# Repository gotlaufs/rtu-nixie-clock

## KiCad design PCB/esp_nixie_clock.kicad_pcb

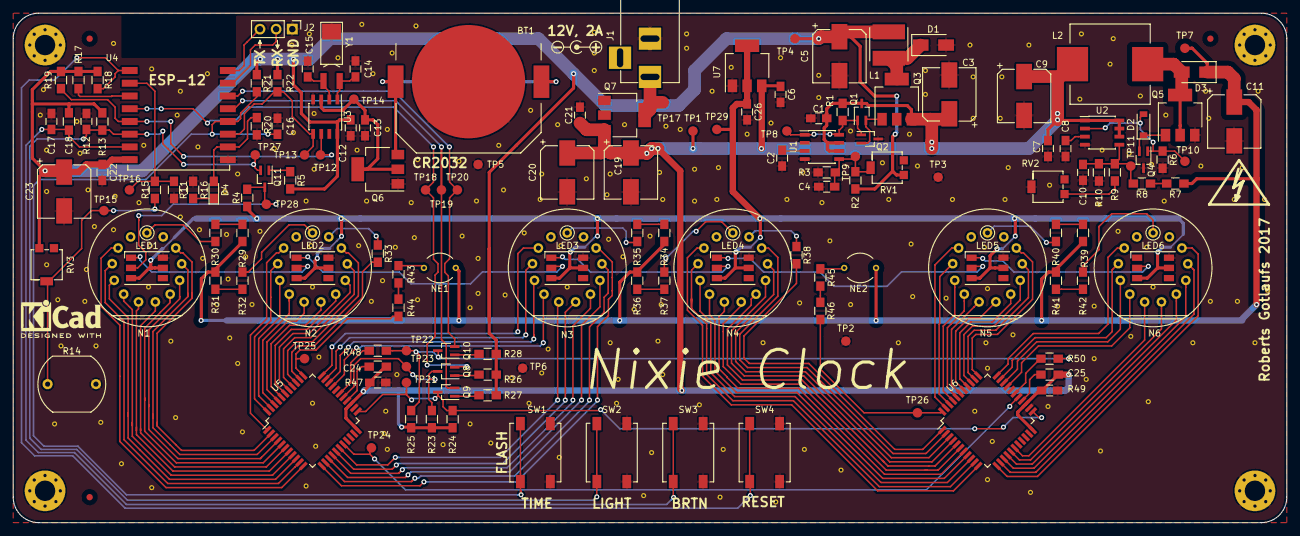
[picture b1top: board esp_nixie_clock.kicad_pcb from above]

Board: 2 copper layers, 200.0 x 80.0 mm, 161 parts (0 on the bottom side), 138 nets.

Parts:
BT1: CR2032; BATT_HOLDER
C1, C6, C7, C12, C13, C16, C17, C18, C21, C22, C24, C25, C26: 100n; C_0805_HandSoldering
C2: 270p; C_0805_HandSoldering
C3, C5, C9, C19: 220u; CP_Elec_8x10
C4, C10: 10n; C_0805_HandSoldering
C8: 680p; C_0805_HandSoldering
C11: 2.2u; CP_Elec_8x10
C14, C15: 6p; C_0805_HandSoldering
C20: 1u; CP_Elec_8x10
C23: 10u; CP_Elec_8x10
D1: SS13 R3G; D_SMA
D2: 1n4148; D_SOD-123
D3: RS1GTR; D_SMA
D4: LED; LED_0805_HandSoldering
F1, F2, F3: Fiducial; Fiducial_1mm_Dia_2.54mm_Outer_CopperTop
J1: Power Jack; BARREL_JACK
J2: Conn_01x03_Male; Pin_Header_Straight_1x03_Pitch2.54mm
L1: 100u; L_100u
L2: 150u; L_Wuerth_WE-PD-Typ-LS_Handsoldering
LED1, LED2, LED3, LED4, LED5, LED6: WS2812; LED_WS2812-PLCC6
MK1, MK2, MK3, MK4: Mounting_Hole_PAD; MountingHole_3.2mm_M3_Pad_Via
N1, N2, N3, N4, N5, N6: IN-14
NE1, NE2: Lamp_Neon; NE-2
Q1, Q8, Q9, Q10, Q11: BC847BW; SOT-323_SC-70_Handsoldering
Q2, Q4: BC857W; SOT-323_SC-70_Handsoldering
Q3, Q6, Q7: NTF5P03T3G; SOT-223-3_TabPin2
Q5: IPN70R900P7SATMA1; SOT-223-3_TabPin2
R1, R5, R6, R26, R27, R28: 1k; R_0805_HandSoldering
R2, R10: 5.6k; R_0805_HandSoldering
R3, R9: 3.3k; R_0805_HandSoldering
R4, R12, R13, R17, R18, R19, R20, R21, R22, R23, R24, R25: 10k; R_0805_HandSoldering
R7, R8: 165k; R_0805_HandSoldering
R11: 300; R_0805_HandSoldering
R14: LDR; Resistor_LDR_10x8.5_RM7.6
R15: 330k; R_0805_HandSoldering
R16, R43, R44, R45, R46: 100k; R_0805_HandSoldering
R29, R30, R31, R32, R34, R35, R36, R37, R39, R40, R41, R42: 5k; R_0805_HandSoldering
R33, R38: 68k; R_0805_HandSoldering
R47, R48, R49, R50: 0R; R_0805_HandSoldering
RV1, RV2, RV3: 100k; Potentiometer_Trimmer_Bourns_3214G
SW1, SW2, SW3, SW4: SW_Push; SW_SMD
TP1, TP2, TP3, TP4, TP5, TP6, TP7, TP8, TP9, TP10, TP11, TP12, TP13, TP14, TP15, TP16, TP17, TP18, TP19, TP20, TP21, TP22, TP23, TP24, TP25, TP26, TP27, TP28, TP29: TestPoint; Measurement_Point_Round-SMD-Pad_Small
U1, U2: MC34063; SOIC-8_3.9x4.9mm_Pitch1.27mm
U3: MCP7940N; SOIC-8_3.9x4.9mm_Pitch1.27mm
U4: ESP-12; ESP-12-SMD
U5, U6: HV5522; PQFP-44_10x10mm_Pitch0.8mm
U7: AZ1117-3.3; SOT-223-3_TabPin2
Y1: 32.768 kHz; Citizen_CMR200T

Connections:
+5V: C26.1, LED1.3, LED1.5, LED2.3, LED2.5, LED3.3, LED3.5, LED4.3, LED4.5, LED5.3, LED5.5, LED6.3, LED6.5, R4.1, TP29.1, U7.2
+12V: C1.1, C3.1, C6.1, C7.1, C9.1, C19.1, C20.1, C21.1, C24.1, C25.1, L2.1, Q1.3, Q3.3, Q7.3, R1.1, R23.1, R24.1, R25.1, R47.1, R49.1, TP1.1, U1.6, U1.7, U2.1, U2.6, U2.7, U2.8, U5.22, U5.25, U6.22, U6.25, U7.3
+HV: C11.1, D3.1, NE1.2, NE2.2, R7.1, R29.1, R31.1, R34.1, R36.1, R39.1, R41.1, TP7.1
/Input power/VIN: J1.1, Q7.2, TP17.1
/MCU ESP-12/CLK: Q9.2, TP19.1, U4.13
/MCU ESP-12/LED_1: D4.2, R20.1, U4.10
/MCU ESP-12/PHOTO: R15.2, R16.1, TP16.1, U4.2
/MCU ESP-12/RXD: J2.2, U4.15
/MCU ESP-12/SCL: R19.2, TP12.1, U3.6, U4.5
/MCU ESP-12/SDA: R22.2, TP13.1, U3.5, U4.11
/MCU ESP-12/SW_2: C17.1, R12.2, SW3.1, U4.7
/MCU ESP-12/SW_3: C16.1, R21.2, SW1.1, U4.12
/MCU ESP-12/TXD: J2.3, U4.16
/MCU ESP-12/~BLANK: Q10.2, TP20.1, U4.14
/Nixie Tube drivers/COLON_1: R44.2, TP25.1, U5.34
/Nixie Tube drivers/COLON_2: R46.2, TP26.1, U6.44
/Nixie Tube drivers/DATA_IN: Q8.2, TP18.1, U4.4
/Nixie Tube drivers/DECIMAL_1: R33.2, U5.35
/Nixie Tube drivers/DECIMAL_2: R38.2, U6.1
/Nixie Tube drivers/N1_0: N1.12, U5.2
/Nixie Tube drivers/N1_1: N1.3, U5.11
/Nixie Tube drivers/N1_2: N1.4, U5.10
/Nixie Tube drivers/N1_3: N1.5, U5.9
/Nixie Tube drivers/N1_4: N1.6, U5.8
/Nixie Tube drivers/N1_5: N1.7, U5.7
/Nixie Tube drivers/N1_6: N1.8, U5.6
/Nixie Tube drivers/N1_7: N1.9, U5.5
/Nixie Tube drivers/N1_8: N1.10, U5.4
/Nixie Tube drivers/N1_9: N1.11, U5.3
/Nixie Tube drivers/N2_0: N2.12, U5.36
/Nixie Tube drivers/N2_1: N2.3, U5.1
/Nixie Tube drivers/N2_2: N2.4, U5.44
/Nixie Tube drivers/N2_3: N2.5, U5.43
/Nixie Tube drivers/N2_4: N2.6, U5.42
/Nixie Tube drivers/N2_5: N2.7, U5.41
/Nixie Tube drivers/N2_6: N2.8, U5.40
/Nixie Tube drivers/N2_7: N2.9, U5.39
/Nixie Tube drivers/N2_8: N2.10, U5.38
/Nixie Tube drivers/N2_9: N2.11, U5.37
/Nixie Tube drivers/N3_0: N3.12, U5.12
/Nixie Tube drivers/N3_1: N3.3, U5.33
/Nixie Tube drivers/N3_2: N3.4, U5.32
/Nixie Tube drivers/N3_3: N3.5, U5.31
/Nixie Tube drivers/N3_4: N3.6, U5.30
/Nixie Tube drivers/N3_5: N3.7, U5.17
/Nixie Tube drivers/N3_6: N3.8, U5.16
/Nixie Tube drivers/N3_7: N3.9, U5.15
/Nixie Tube drivers/N3_8: N3.10, U5.14
/Nixie Tube drivers/N3_9: N3.11, U5.13
/Nixie Tube drivers/N4_0: N4.12, U6.2
/Nixie Tube drivers/N4_1: N4.3, U6.11
/Nixie Tube drivers/N4_2: N4.4, U6.10
/Nixie Tube drivers/N4_3: N4.5, U6.9
/Nixie Tube drivers/N4_4: N4.6, U6.8
/Nixie Tube drivers/N4_5: N4.7, U6.7
/Nixie Tube drivers/N4_6: N4.8, U6.6
/Nixie Tube drivers/N4_7: N4.9, U6.5
/Nixie Tube drivers/N4_8: N4.10, U6.4
/Nixie Tube drivers/N4_9: N4.11, U6.3
/Nixie Tube drivers/N5_0: N5.12, U6.34
/Nixie Tube drivers/N5_1: N5.3, U6.43
/Nixie Tube drivers/N5_2: N5.4, U6.42
/Nixie Tube drivers/N5_3: N5.5, U6.41
/Nixie Tube drivers/N5_4: N5.6, U6.40
/Nixie Tube drivers/N5_5: N5.7, U6.39
/Nixie Tube drivers/N5_6: N5.8, U6.38
/Nixie Tube drivers/N5_7: N5.9, U6.37
/Nixie Tube drivers/N5_8: N5.10, U6.36
/Nixie Tube drivers/N5_9: N5.11, U6.35
/Nixie Tube drivers/N6_0: N6.12, U6.12
/Nixie Tube drivers/N6_1: N6.3, U6.33
/Nixie Tube drivers/N6_2: N6.4, U6.32
/Nixie Tube drivers/N6_3: N6.5, U6.31
/Nixie Tube drivers/N6_4: N6.6, U6.30
/Nixie Tube drivers/N6_5: N6.7, U6.17
/Nixie Tube drivers/N6_6: N6.8, U6.16
/Nixie Tube drivers/N6_7: N6.9, U6.15
/Nixie Tube drivers/N6_8: N6.10, U6.14
/Nixie Tube drivers/N6_9: N6.11, U6.13
/Programmable LEDs/Data_In: C18.1, Q11.2, R13.2, SW2.1, TP27.1, U4.6
/Real Time Clock/BAT_IN: BT1.1, Q6.3
/Real Time Clock/VBAT: C13.1, Q6.2, TP14.1, U3.3
GND: BT1.2, C1.2, C2.2, C3.2, C4.2, C5.2, C6.2, C7.2, C8.2, C9.2, C10.2, C11.2, C12.2, C13.2, C14.2, C15.2, C16.2, C17.2, C18.2, C19.2, C20.2, C21.2, C22.2, C23.2, C24.2, C25.2, C26.2, D1.2, J1.2, J2.1, LED1.6, LED2.6, LED3.6, LED4.6, LED5.6, LED6.6, MK1.1, MK2.1, MK3.1, MK4.1, Q2.3, Q4.3, Q5.3, Q6.1, Q7.1, R3.2, R6.2, R9.2, R11.2, R14.2, R16.2, R20.2, RV2.2, SW1.2, SW2.2, SW3.2, SW4.2, TP2.1, TP3.1, TP5.1, TP6.1, U1.2, U1.4, U2.4, U3.4, U4.9, U5.24, U6.24, U7.1, Y1.3
unnamed: C2.1, U1.3
unnamed: C4.1, R2.2, R3.1, RV1.2, TP9.1, U1.5
unnamed: C8.1, U2.3
unnamed: C10.1, R8.2, R9.1, R10.2, TP11.1, U2.5
unnamed: C14.1, U3.1, Y1.1
unnamed: C15.1, U3.2, Y1.2
unnamed: D1.1, L1.1, Q3.2
unnamed: D2.1, Q4.2, Q5.1
unnamed: D2.2, Q4.1, R6.1, TP10.1, U2.2
unnamed: D3.2, L2.2, Q5.2
unnamed: D4.1, R11.1
unnamed: LED1.1, LED2.2
unnamed: LED1.2, Q11.3, R4.2, TP28.1
unnamed: LED2.1, LED3.2
unnamed: LED3.1, LED4.2
unnamed: LED4.1, LED5.2
unnamed: LED5.1, LED6.2
unnamed: N1.1, R30.2
unnamed: N2.1, R32.2
unnamed: N2.13, R33.1
unnamed: N3.1, R35.2
unnamed: N4.1, R37.2
unnamed: N4.13, R38.1
unnamed: N5.1, R40.2
unnamed: N6.1, R42.2
unnamed: NE1.1, R43.1
unnamed: NE2.1, R45.1
unnamed: Q1.1, Q2.1, R1.2, TP8.1, U1.1, U1.8
unnamed: Q1.2, Q2.2, Q3.1
unnamed: Q8.1, R26.2
unnamed: Q8.3, R23.2, TP23.1, U5.27
unnamed: Q9.1, R27.2
unnamed: Q9.3, R24.2, TP21.1, U5.23, U6.23
unnamed: Q10.1, R28.2
unnamed: Q10.3, R25.2, R48.1, R50.1, TP22.1
unnamed: Q11.1, R5.2
unnamed: R7.2, R8.1
unnamed: R10.1, RV2.3
unnamed: R14.1, R15.1, RV3.2, TP15.1
unnamed: R17.2, U4.3
unnamed: R18.2, SW4.1, U4.1
unnamed: R29.2, R30.1
unnamed: R31.2, R32.1
unnamed: R34.2, R35.1
unnamed: R36.2, R37.1
unnamed: R39.2, R40.1
unnamed: R41.2, R42.1
unnamed: R43.2, R44.1
unnamed: R45.2, R46.1
unnamed: R47.2, U5.26
unnamed: R48.2, U5.28
unnamed: R49.2, U6.26
unnamed: R50.2, U6.28
unnamed: TP24.1, U5.18, U6.27
VCC: C5.1, C12.1, C22.1, C23.1, L1.2, R2.1, R5.1, R12.1, R13.1, R17.1, R18.1, R19.1, R21.1, R22.1, R26.1, R27.1, R28.1, RV1.3, RV3.1, TP4.1, U3.8, U4.8

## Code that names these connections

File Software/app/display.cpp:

#include "display.h"
// #include "lean_time.h"
#include "nixie_driver.h"

#include <SmingCore/SmingCore.h>

void show_time_simple(void){

    time_t now = RTC.getRtcSeconds();
    nixie_data_type nixie_data;

    int8_t sec, min, hour;
    DateTime::fromUnixTime(now, &sec, &min, &hour, NULL, NULL, NULL, NULL);

    nixie_data.N6 = sec % 10;
    nixie_data.N5 = sec / 10;

    nixie_data.N4 = min % 10;
    nixie_data.N3 = min / 10;

    nixie_data.N2 = hour % 10;
    nixie_data.N1 = hour / 10;

    nixie_data.DECIMAL_1 = 0;
    nixie_data.DECIMAL_2 = 0;

    nixie_data.COLON_1 = 1;
    nixie_data.COLON_2 = 1;

    nixie_update(&nixie_data);
}

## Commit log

2019-01-02 First commit. Add everything
2019-01-03 Move old source files to separate dir
2019-01-03 Add basic Sming Blink project
2019-01-03 Remove build files
2019-01-03 Port old SDK app to Sming
2019-01-03 'out' dir should be kept
2019-01-08 Move to using Sming's implementation of DateTime
2019-01-08 Add Eclipse project
2019-01-17 Add MCP7940 files from other project and begin experimenting with I2C
2019-01-30 Figure out how to run RTC correctly
2019-01-30 Fix errors that prevent compilation
2019-01-31 Fix wrong RTC initialization
2019-01-31 Experiments with Interrupts. SW3 does not seem to be working
2019-02-04 Start making Button class for event detection
2019-02-05 Use lambdas for ISRs
2019-02-10 Add state machine to handle various display modes
2019-02-10 Add simple serial button faker
2019-02-11 Add update() method for state class
2019-02-16 Enable numbers 3&4 on Nixie Tube N5. Seems like the electrical short is gone
2019-02-17 Make colons blink
2019-02-17 Use Button class for all tactile switches
2019-02-19 Try getting time setting to work
2019-02-19 Time setting works, but is flakey
2019-02-19 Fix flakiness in setting time to external RTC
2019-12-01 Add tube saver state
2019-12-01 Mostly finish logic for tube saver and make it compile
2019-12-01 Run tube saver every hour
2019-12-01 Show sceensaver when the device boots
2019-12-01 Remove debug prints and fix annoying zeros
